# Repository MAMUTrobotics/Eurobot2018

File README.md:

# Eurobot2018

Anmerkungen bzgl. der Gestaltung des Roboters von David Buhren:
Ich habe mir ein paar Gedanken gemacht, welche Komponenten der Roboter haben sollte.
- Vorausgesetzt man fährt ausschließlich vorwärts und niemals rückwärts, so ist es okay wenn man auf der Rückseite keine Sensoren anbringt. Es sollte daher reichen, wenn vorne mehrer nach vorn gerichtete Distanzsensoren angebracht sind, die sowohl Gegner, als auch Wände detektieren.
- Es sollte angestrebt werden, für jede Roboteraktion möglichst nur einen Aktor zu verwenden.
- Der Bau von Gebäuden entsprechend der Konstruktionsvorschriften ist sehr aufwendig (Bildverarbeitung + Sortierung + Stapeln). Daher schlage ich vor, wir verwenden einfach zwei vor dem Roboter angebrachte Walzen, um Würfel die der Roboter vor sich herschiebt bei Wandkontakt nach oben umzuwälzen. Die Würfel sind dann zwar nicht sortiert, aber sie sind zumindest teilweise gestapelt und platzsparend in der Bauzone abgelegt.
- Die Wasserkugeln können ähnlich mit Hilfe einer größeren Variante unserer Raketenabschussvorrichtung von diesem Jahr mit nur einem Aktor in den Tank geschossen werden. Zum Ablegen in die Kläranlage kann eine Auslassklappe verwendet werden, welche die in einer Schale gesammelten Wasserkugeln direkt ins Klärbecken abläßt. Die Wasserspender werden mit einem kleinen starken Stab, welcher sich radial um eine vertikale Achse dreht entleert. Die Wasserkugeln sollen dann direkt in eine hoch gelegene weiche Schale fallen, die dann sowohl für den Transport zur Kläranlage, als auch zum Tank genutzt werden können.
- Da viele Aktoren und Sensoren auf der Vorderseite des Roboters angebracht werden, kann auf der Heckseite das Bedienpult und der Akku positioniert werden.

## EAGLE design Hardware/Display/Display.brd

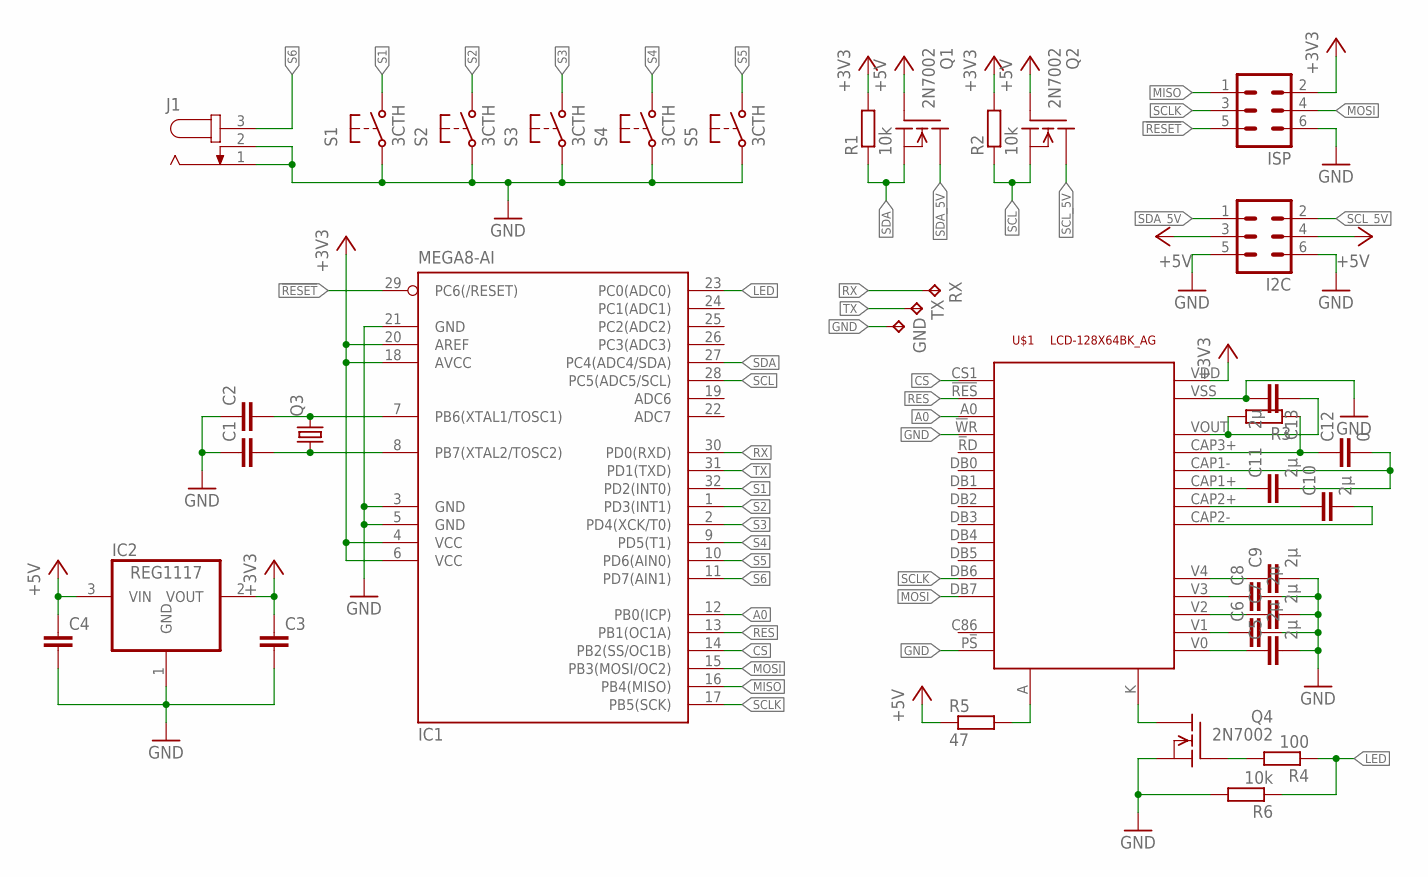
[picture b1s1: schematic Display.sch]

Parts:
C1, C2, C3, C4: C-EUC0805K; C0805K
C5, C6, C7, C8, C9, C10, C11, C13: 2µ; C0805K
C12: 0; C0805K
GND: TPPAD1-13; P1-13
I2C: ML6
IC1: MEGA8-AI; TQFP32-08
IC2: REG1117; SOT223
ISP: ML6
J1: JACK-PLUG0; SPC4077
Q1, Q2, Q4: 2N7002; SOT23
Q3: CRYSTALHC49UP; HC49UP
R1, R2, R6: 10k; R0805
R3: R-EU_R0805; R0805
R4: 100; R0805
R5: 47; 0207/10
RX: TPPAD1-13; P1-13
S1, S2, S3, S4, S5: 3CTH
TX: TPPAD1-13; P1-13
U$1: LCD-128X64BK_AG

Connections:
!RESET: IC1.29 (PC6(/RESET)), ISP.5
+3V3: C3.1, IC1.4 (VCC), IC1.6 (VCC), IC1.18 (AVCC), IC1.20 (AREF), IC2.2 (VOUT), ISP.2, R1.2, R2.2, U$1.VDD
+5V: C4.1, I2C.3, I2C.4, IC2.3 (VIN), Q1.1 (G), Q2.1 (G), R5.1
A0: IC1.12 (PB0(ICP)), U$1.A0
CS: IC1.14 (PB2(SS/OC1B)), U$1.CS1
GND: C1.1, C2.1, C3.2, C4.2, C5.2, C6.2, C7.2, C8.2, C9.2, C13.2, GND.TP, I2C.5, I2C.6, IC1.3 (GND), IC1.5 (GND), IC1.21 (GND), IC2.1 (GND), ISP.6, J1.1, J1.2, Q4.2 (S), R6.2, S1.3, S1.4, S2.3, S2.4, S3.3, S3.4, S4.3, S4.4, S5.3, S5.4, U$1.!W!R, U$1.P!S, U$1.VSS
LED: IC1.23 (PC0(ADC0)), R4.1, R6.1
MISO: IC1.16 (PB4(MISO)), ISP.1
MOSI: IC1.15 (PB3(MOSI/OC2)), ISP.4, U$1.DB7
unnamed: Q4.3 (D), U$1.K
unnamed: C1.2, IC1.8 (PB7(XTAL2/TOSC2)), Q3.1
unnamed: C2.2, IC1.7 (PB6(XTAL1/TOSC1)), Q3.2
unnamed: C13.1, R3.2, U$1.VOUT
unnamed: Q4.1 (G), R4.2
unnamed: C12.1, R3.1, U$1.CAP3+
unnamed: R5.2, U$1.A
unnamed: C11.2, C12.2, U$1.CAP1-
unnamed: C11.1, U$1.CAP1+
unnamed: C10.1, U$1.CAP2+
unnamed: C10.2, U$1.CAP2-
unnamed: C9.1, U$1.V4
unnamed: C8.1, U$1.V3
unnamed: C7.1, U$1.V2
unnamed: C6.1, U$1.V1
unnamed: C5.1, U$1.V0
RES: IC1.13 (PB1(OC1A)), U$1.!RES
RX: IC1.30 (PD0(RXD)), RX.TP
S1: IC1.32 (PD2(INT0)), S1.1 (S), S1.2 (S)
S2: IC1.1 (PD3(INT1)), S2.1 (S), S2.2 (S)
S3: IC1.2 (PD4(XCK/T0)), S3.1 (S), S3.2 (S)
S4: IC1.9 (PD5(T1)), S4.1 (S), S4.2 (S)
S5: IC1.10 (PD6(AIN0)), S5.1 (S), S5.2 (S)
S6: IC1.11 (PD7(AIN1)), J1.3
SCL: IC1.28 (PC5(ADC5/SCL)), Q2.2 (S), R2.1
SCLK: IC1.17 (PB5(SCK)), ISP.3, U$1.DB6
SCL_5V: I2C.2, Q2.3 (D)
SDA: IC1.27 (PC4(ADC4/SDA)), Q1.2 (S), R1.1
SDA_5V: I2C.1, Q1.3 (D)
TX: IC1.31 (PD1(TXD)), TX.TP

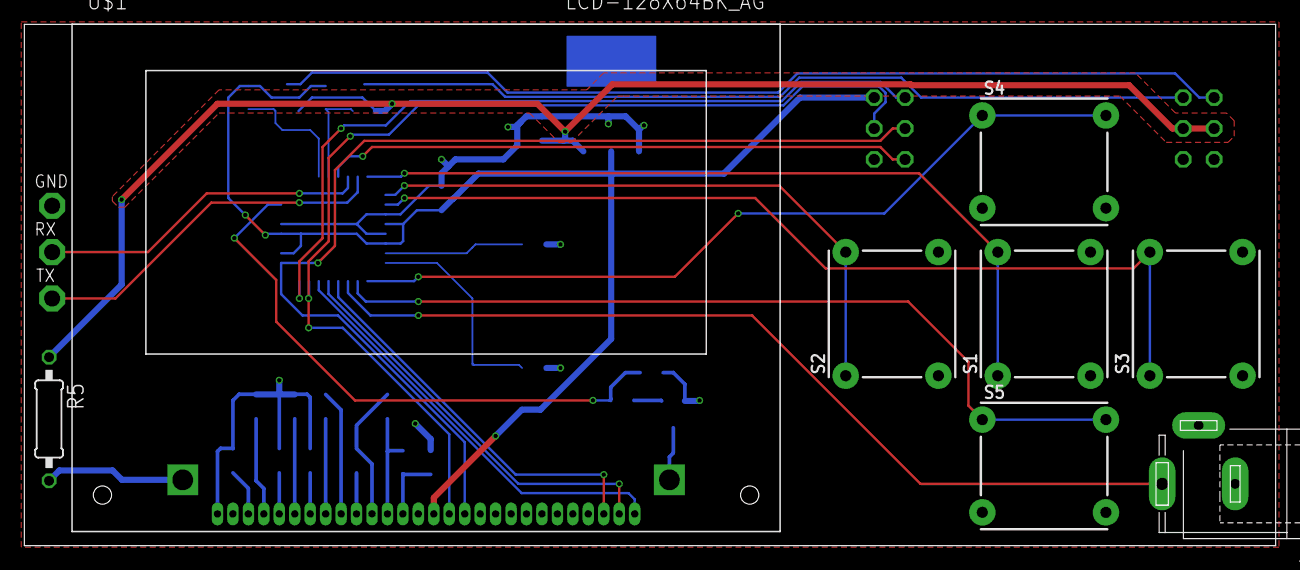
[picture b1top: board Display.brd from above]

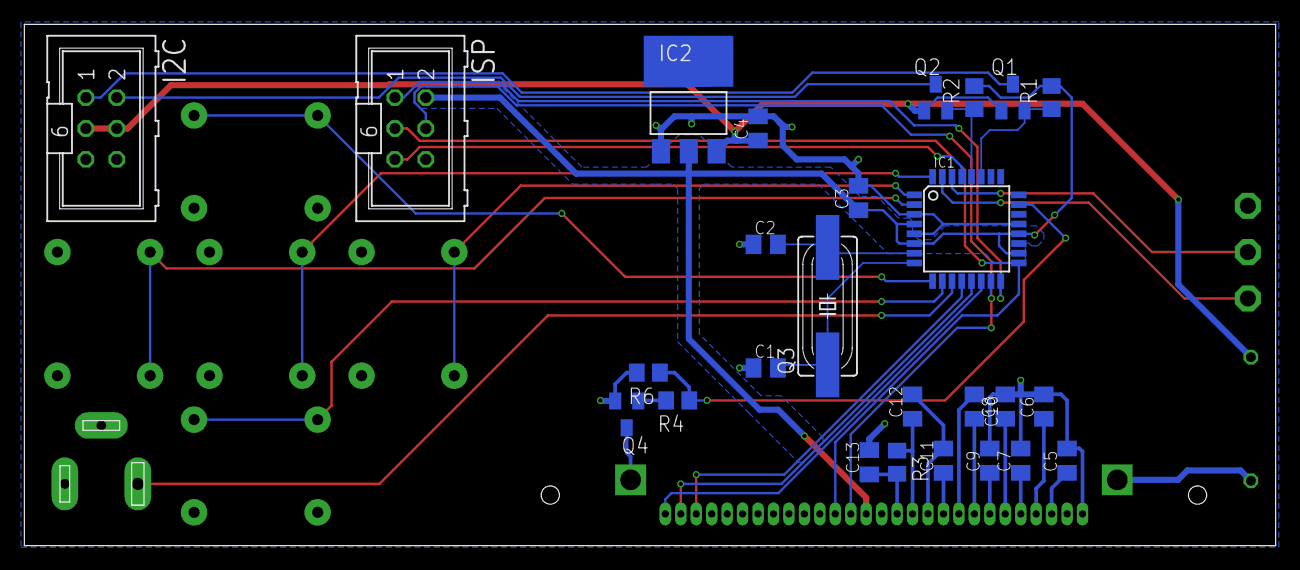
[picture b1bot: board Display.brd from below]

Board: 2 copper layers, 102.9 x 42.9 mm, 37 parts (26 on the bottom side), 39 nets.

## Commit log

2017-10-15 Create Remote controlled RP6
2017-10-16 Final_Rules
2017-10-19 Add files via upload
    Ich habe mir ein paar Gedanken gemacht, welche Komponenten der Roboter haben sollte.
    - Vorausgesetzt man fährt ausschließlich vorwärts und niemals rückwärts, so ist es okay wenn man auf der Rückseite keine Sensoren anbringt. Es sollte daher reichen, wenn vorne mehrer nach vorn gerich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
    - Es sollte angestrebt werden, für jede Roboteraktion möglichst nur einen Aktor zu verwenden.
    - Der Bau von Gebäuden entsprechend der Konstruktionsvorschriften ist sehr aufwendig (Bildverarbeitung + Sortierung + Stapeln). Daher schlage ich vor, wir verwenden einfach zwei vor dem Roboter angeb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
2017-10-29 Now the robot follow double lines
2017-11-21 Aktualisierter Ablaufplan sowie Abbildung des korrekten Spielfelds
2017-12-04 aktueller_stand
2018-01-25 Add Schmatic/Layout (Display)
2018-02-28 CAD Roboterplatform
2018-02-28 CAD Odometrie (Soppa)
2018-02-28 Odometrie zu Fahrbasis hizugefügt
2018-03-15 Display und Halterung in 3D
2018-04-13 Code für LCD
    Nicht schön aber selten.
2018-04-13 Clear Debug
2018-04-13 Update gitignore
2018-04-13 Add hex file
2018-04-18 Code upload
2018-04-25 3D-Konstruktion
2018-05-01 Update-LCD
2018-05-02 CAD Fahrbasis Aktualisiert
2018-05-02 Ausrichtung der Fahrbasis korrigiert

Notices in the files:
parts and their libraries:
switch-mec: Copyright (C) 2012, Bob Starr
